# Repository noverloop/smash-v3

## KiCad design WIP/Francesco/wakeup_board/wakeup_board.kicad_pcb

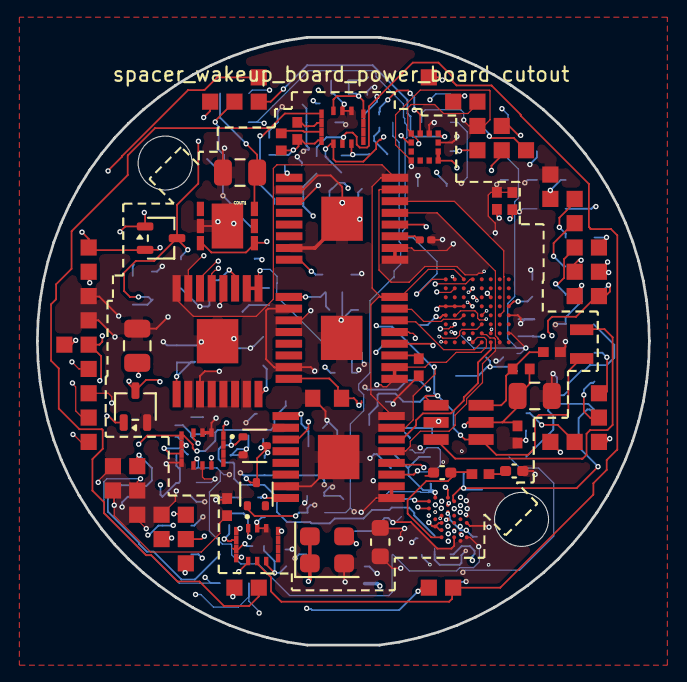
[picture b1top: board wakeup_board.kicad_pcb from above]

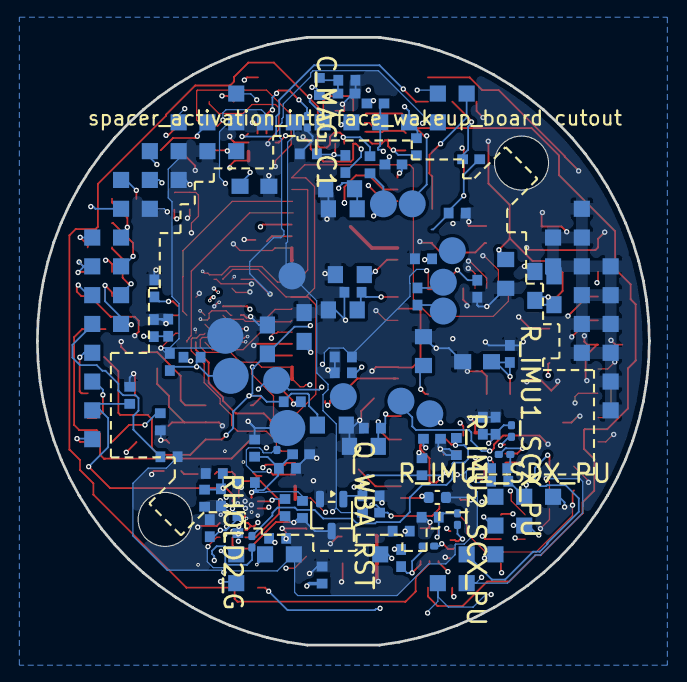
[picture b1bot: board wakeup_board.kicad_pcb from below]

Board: 14 copper layers, 34.0 x 33.8 mm, 127 parts (90 on the bottom side), 109 nets.

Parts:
CBOOST_IN1_1, CBOOST_IN1_2, CBOOST_IN1_3, CBOOST_IN1_4, CBOOST_IN1_5: C-Series MIL-PRF-32535 X7R 0603 2.2uF; C_0603_1608Metric
CBOOST_IN2: C0402 X7R 100nF; C_0402_1005Metric
CBOOST_OUT1: 22uF 16V X5R 0805; C_0805_2012Metric
CBOOST_OUT2: C0402 X7R 100nF; C_0402_1005Metric
CMAIN_HOLD: C0402 X7R 100nF; C_0402_1005Metric
COUT1: T491T 22uF (3528-12 thinnest variant); C_0805_2012Metric
COUT2: 22uF 16V X5R 0805; C_0805_2012Metric
COUT3: C0402 X7R 100nF; C_0402_1005Metric
C_CAM_VDD: C0402 X7R 100nF; C_0402_1005Metric
C_FIN1_DVDD, C_FIN3_DVDD, C_FIN4_DVDD: C-Series MIL-PRF-32535 X7R 0805 1uF; C_0603_1608Metric
C_FIN1_VM, C_FIN2_VM, C_FIN3_VM, C_FIN4_VM: C0402 X7R 100nF; C_0402_1005Metric
C_FIN2_DVDD: C-Series MIL-PRF-32535 X7R 0805 1uF; C_0402_1005Metric
C_FIN_VM_BULK_1, C_FIN_VM_BULK_2, C_FIN_VM_BULK_3, C_FIN_VM_BULK_4, C_FIN_VM_BULK_5: C-Series MIL-PRF-32535 X7R 0603 2.2uF; C_0603_1608Metric
C_FIN_VREF: C0402 X7R 100nF; C_0402_1005Metric
C_G0B1_FIN_BULK: C-Series MIL-PRF-32535 X7R 0805 1uF; C_0603_1608Metric
C_G0B1_FIN_NRST, C_G0B1_FIN_VDD1, C_G0B1_FIN_VDD2, C_G0B1_FIN_VREF: C0402 X7R 100nF; C_0402_1005Metric
C_IMU1_1, C_IMU2_1, C_IMU3_1: C0402 X7R 100nF; C_0402_1005Metric
C_IMU1_2, C_IMU2_2, C_IMU3_2: C-Series MIL-PRF-32535 X7R 0603 2.2uF; C_0402_1005Metric
C_IMU1_3, C_IMU2_3, C_IMU3_3: C0402 X7R 10nF; C_0402_1005Metric
C_J_HALL_FIN_VCC: C0402 X7R 100nF; C_0402_1005Metric
C_MAG1: C0402 X7R 100nF; C_0402_1005Metric
C_MAG2: C-Series MIL-PRF-32535 X7R 0805 1uF; C_0603_1608Metric
C_MAG_C1: C-Series MIL-PRF-32535 X7R 0603 220nF; R_0201_0603Metric
C_WBA_BULK_1, C_WBA_BULK_2: C-Series MIL-PRF-32535 X7R 0603 2.2uF; C_0402_1005Metric
C_WBA_HSE_VDD: C0402 X7R 100nF; C_0402_1005Metric
C_WBA_NRST: C0402 X7R 100nF; C_0402_1005Metric
C_WBA_PI1, C_WBA_PI2: SQCSVA 0.5pF; C_0402_1005Metric
C_WBA_VDD1, C_WBA_VDD2: C0402 X7R 100nF; C_0402_1005Metric
C_WBA_VDD11: C-Series MIL-PRF-32535 X7R 0603 2.2uF; C_0402_1005Metric
C_WBA_VDDA: C0402 X7R 100nF; C_0402_1005Metric
C_WBA_VDDANA: C0402 X7R 100nF; C_0402_1005Metric
C_WBA_VDDHPA: C0402 X7R 100nF; C_0402_1005Metric
C_WBA_VDDRF: C0402 X7R 100nF; C_0402_1005Metric
C_WBA_VDDRFPA: C0402 X7R 100nF; C_0402_1005Metric
C_WBA_VDDSMPS: C0402 X7R 100nF; C_0402_1005Metric
D_NFC_WAKE: BAT64-06-TP; SOT-523
J_HALL_FIN_GND: J_HALL_FIN_GND; Pogo_Pad_D2.0mm
J_HALL_FIN_OUT: J_HALL_FIN_OUT; Pogo_Pad_D2.0mm
J_HALL_FIN_VCC: J_HALL_FIN_VCC; Pogo_Pad_D2.0mm
J_wakeup_board_spacer_wakeup_board_power_board: LGA_lands; J_wakeup_board_spacer_wakeup_board_power_board
L_PWR: TMS201210ALM-2R2MTAA; L_2012_2.0x1.25mm
L_WBA_PI: WE-KI 0402 2.7nH (74479xxxxx family); L_0402_1005Metric
L_WBA_SMPS: TMS201210ALM-2R2MTAA; L_0603_1608Metric
P_wakeup_board_spacer_activation_interface_wakeup_board: LGA_lands; P_wakeup_board_spacer_activation_interface_wakeup_board
QHOLD: BSS138LT1G; SOT-323_SC-70
QHOLD2: BSS138LT1G; SOT-523
QMAIN: DMP2165UW-7; SOT-323_SC-70
Q_WBA_RST: BSS138LT1G; SOT-323_SC-70
RHOLD2_G: CRCW0402 100 1% e3; R_0201_0603Metric
RHOLD2_PD: CRCW0402 100k 1% e3; R_0402_1005Metric
RHOLD_AON: CRCW0402 1k 1% e3; R_0402_1005Metric
RHOLD_G: CRCW0402 100 1% e3; R_0402_1005Metric
RHOLD_PD: CRCW0402 100k 1% e3; R_0402_1005Metric
RMAIN_PU: CRCW0402 1M 1% e3; R_0402_1005Metric
RPU_I2C2_SCL, RPU_I2C2_SDA, RPU_I2C3_SCL, RPU_I2C3_SDA: CRCW0402 4.7k 1% e3; R_0402_1005Metric
RPU_SCL_EXT: CRCW0402 4.7k 1% e3; R_0402_1005Metric
RPU_SDA_EXT: CRCW0402 4.7k 1% e3; R_0402_1005Metric
R_BOOST_FB1: CRCW0402 220k 1% e3; R_0402_1005Metric
R_BOOST_FB2: CRCW0402 100k 1% e3; R_0402_1005Metric
R_FIN1_DECAY, R_FIN4_DECAY: CRCW0402 44.2k 1% e3; R_0402_1005Metric
R_FIN2_DECAY, R_FIN3_DECAY: CRCW0402 44.2k 1% e3; R_0201_0603Metric
R_G0B1_FIN_NRST: CRCW0402 10k 1% e3; R_0402_1005Metric
R_IMU1_SCX_PU, R_IMU1_SDX_PU, R_IMU2_SCX_PU, R_IMU2_SDX_PU: CRCW0402 10k 1% e3; R_0201_0603Metric
R_IMU3_SCX_PU, R_IMU3_SDX_PU: CRCW0402 10k 1% e3; R_0402_1005Metric
R_J_HALL_FIN_PU: CRCW0402 10k 1% e3; R_0402_1005Metric
R_NFC_WAKE: CRCW0402 3.3k 1% e3; R_0402_1005Metric
R_WBARST_PD: CRCW0402 100k 1% e3; R_0402_1005Metric
R_WBA_BOOT0: CRCW0402 10k 1% e3; R_0402_1005Metric
R_WBA_NRST: CRCW0402 10k 1% e3; R_0402_1005Metric
R_WILK_ISO: CRCW0402 100 1% e3; R_0402_1005Metric
TP_3V3: TP_3V3; TestPoint_Pad_D1.5mm
TP_BAT: TP_BAT; TestPoint_Pad_D1.5mm
TP_IMU1_INT: TP_IMU1_INT; TestPoint_Pad_D1.5mm
TP_IMU2_INT: TP_IMU2_INT; TestPoint_Pad_D1.5mm
TP_IMU3_INT: TP_IMU3_INT; TestPoint_Pad_D1.5mm
TP_NFC_GPO: TP_NFC_GPO; TestPoint_Pad_D1.5mm
TP_WILK_A: TP_WILK_A; TestPoint_Pad_D1.5mm
TP_WILK_B: TP_WILK_B; TestPoint_Pad_D1.5mm
TP_YAGI_RF_A: TP_YAGI_RF_A; TestPoint_Pad_D1.5mm
TP_YAGI_RF_B: TP_YAGI_RF_B; TestPoint_Pad_D1.5mm
U_BOOST: MCP1640CT-I/CHY; SOT95P270X145-6N
U_FIN1, U_FIN2, U_FIN3, U_FIN4: DRV8428EPWPR; SOP65P640X120-17N
U_G0B1_FIN: STM32G0B1REI6N; BGA64C50P8X8_500X500X60
U_IMU1, U_IMU2, U_IMU3: ISM330DHCXTR; LSM6DS3USTR (LGA-14)
U_MAG: IIS2MDCTR
U_PWR: LDL112PV33R; SON95P300X300X100-7N-D
U_WBA: STM32WBA55HGF6TR; BGA41C35P13X7_298X276X50
Y_WBA_HSE: DSC1001CI5-032.0000; Oscillator_SMD_SiT_PQFN-4Pin_2.5x2.0mm

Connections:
3V3: COUT1.1, COUT2.1, COUT3.1, C_G0B1_FIN_BULK.1, C_G0B1_FIN_VDD1.1, C_G0B1_FIN_VDD2.1, C_G0B1_FIN_VREF.1, C_IMU1_1.1, C_IMU1_2.1, C_IMU1_3.1, C_IMU2_1.1, C_IMU2_2.1, C_IMU2_3.1, C_IMU3_1.1, C_IMU3_2.1, C_IMU3_3.1, C_J_HALL_FIN_VCC.1, C_MAG1.1, C_MAG2.1, J_HALL_FIN_VCC.1, J_wakeup_board_spacer_wakeup_board_powe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.1, J_wakeup_board_spacer_wakeup_board_powe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.49, P_wakeup_board_spacer_activation_interf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.1, P_wakeup_board_spacer_activation_interf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.42, P_wakeup_board_spacer_activation_interf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.47, RPU_I2C2_SCL.1, RPU_I2C2_SDA.1, RPU_I2C3_SCL.1, RPU_I2C3_SDA.1, RPU_SCL_EXT.1, RPU_SDA_EXT.1, R_G0B1_FIN_NRST.1, R_IMU1_SCX_PU.1, R_IMU1_SDX_PU.1, R_IMU2_SCX_PU.1, R_IMU2_SDX_PU.1, R_IMU3_SCX_PU.1, R_IMU3_SDX_PU.1, R_J_HALL_FIN_PU.1, TP_3V3.1, U_G0B1_FIN.D1, U_G0B1_FIN.D2, U_G0B1_FIN.D3, U_G0B1_FIN.D8, U_IMU1.5, U_IMU1.8, U_IMU1.12, U_IMU2.5, U_IMU2.8, U_IMU2.12, U_IMU3.1, U_IMU3.5, U_IMU3.8, U_IMU3.12, U_MAG.3, U_MAG.9, U_MAG.10, U_PWR.4
3V3_AON: C_WBA_BULK_1.1, C_WBA_BULK_2.1, C_WBA_HSE_VDD.1, C_WBA_VDD1.1, C_WBA_VDD2.1, C_WBA_VDDA.1, C_WBA_VDDANA.1, C_WBA_VDDHPA.1, C_WBA_VDDRF.1, C_WBA_VDDRFPA.1, C_WBA_VDDSMPS.1, P_wakeup_board_spacer_activation_interf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.2, P_wakeup_board_spacer_activation_interf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.43, R_WBA_NRST.1, U_WBA.A6, U_WBA.A10, U_WBA.B5, U_WBA.B13, U_WBA.C4, U_WBA.C6, U_WBA.E12, U_WBA.G4, Y_WBA_HSE.1, Y_WBA_HSE.4
ACTIVATE_CONFIRM: J_wakeup_board_spacer_wakeup_board_powe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.2, P_wakeup_board_spacer_activation_interf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.3
ACTIVATE_SET: J_wakeup_board_spacer_wakeup_board_powe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.3, P_wakeup_board_spacer_activation_interf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.4
AON_EN: P_wakeup_board_spacer_activation_interf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.5, RHOLD_AON.2
BAT_PROT: J_wakeup_board_spacer_wakeup_board_powe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.4, J_wakeup_board_spacer_wakeup_board_powe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.50, P_wakeup_board_spacer_activation_interf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.6, P_wakeup_board_spacer_activation_interf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.44, QMAIN.2, TP_BAT.1
BAT_RAW: J_wakeup_board_spacer_wakeup_board_powe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.5, J_wakeup_board_spacer_wakeup_board_powe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.51, P_wakeup_board_spacer_activation_interf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.7, P_wakeup_board_spacer_activation_interf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.45, RMAIN_PU.1
BOOST_FB: R_BOOST_FB1.2, R_BOOST_FB2.1, U_BOOST.4
BOOST_OUT: CBOOST_OUT1.1, CBOOST_OUT2.1, R_BOOST_FB1.1, U_BOOST.5, U_PWR.1, U_PWR.6
BOOST_SW: L_PWR.2, U_BOOST.1
BOOT0: J_wakeup_board_spacer_wakeup_board_powe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.6, P_wakeup_board_spacer_activation_interf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.8
COMP_1V8: C_CAM_VDD.1, J_wakeup_board_spacer_wakeup_board_powe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.7
COMP_5V: J_wakeup_board_spacer_wakeup_board_powe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.8, P_wakeup_board_spacer_activation_interf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.9, P_wakeup_board_spacer_activation_interf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.46
COMP_5V_RAW: C_FIN1_VM.1, C_FIN2_VM.1, C_FIN3_VM.1, C_FIN4_VM.1, C_FIN_VM_BULK_1.1, C_FIN_VM_BULK_2.1, C_FIN_VM_BULK_3.1, C_FIN_VM_BULK_4.1, C_FIN_VM_BULK_5.1, J_wakeup_board_spacer_wakeup_board_powe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.9, U_FIN1.1, U_FIN2.1, U_FIN3.1, U_FIN4.1
COMP_OUT: J_wakeup_board_spacer_wakeup_board_powe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.10, P_wakeup_board_spacer_activation_interf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.10
COMP_SWDCLK: J_wakeup_board_spacer_wakeup_board_powe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.11, P_wakeup_board_spacer_activation_interf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.11
COMP_SWDIO: J_wakeup_board_spacer_wakeup_board_powe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.12, P_wakeup_board_spacer_activation_interf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.12
EXT_CAN_RX: J_wakeup_board_spacer_wakeup_board_powe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.13, P_wakeup_board_spacer_activation_interf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.13
EXT_CAN_TX: J_wakeup_board_spacer_wakeup_board_powe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.14, P_wakeup_board_spacer_activation_interf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.14
FIN1_AEN: U_FIN1.15, U_G0B1_FIN.E3
FIN1_AOUT1: P_wakeup_board_spacer_activation_interf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.15, U_FIN1.3
FIN1_APH: U_FIN1.14, U_G0B1_FIN.H5
FIN1_BEN: U_FIN1.13, U_G0B1_FIN.F5
FIN1_BPH: U_FIN1.12, U_G0B1_FIN.B4
FIN1_DECAY: R_FIN1_DECAY.1, U_FIN1.11
FIN1_DVDD: C_FIN1_DVDD.1, U_FIN1.8
FIN2_AEN: U_FIN2.15, U_G0B1_FIN.F2
FIN2_AOUT1: P_wakeup_board_spacer_activation_interf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.16, U_FIN2.3
FIN2_APH: U_FIN2.14, U_G0B1_FIN.H6
FIN2_BEN: U_FIN2.13, U_G0B1_FIN.G5
FIN2_BPH: U_FIN2.12, U_G0B1_FIN.C4
FIN2_DECAY: R_FIN2_DECAY.1, U_FIN2.11
FIN2_DVDD: C_FIN2_DVDD.1, U_FIN2.8
FIN3_AEN: U_FIN3.15, U_G0B1_FIN.G2
FIN3_AOUT1: P_wakeup_board_spacer_activation_interf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.17, U_FIN3.3
FIN3_APH: U_FIN3.14, U_G0B1_FIN.E7
FIN3_BEN: U_FIN3.13, U_G0B1_FIN.H7
FIN3_BPH: U_FIN3.12, U_G0B1_FIN.D4
FIN3_DECAY: R_FIN3_DECAY.1, U_FIN3.11
FIN3_DVDD: C_FIN3_DVDD.1, U_FIN3.8
FIN4_AEN: U_FIN4.15, U_G0B1_FIN.H1
FIN4_AOUT1: P_wakeup_board_spacer_activation_interf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.18, U_FIN4.3
FIN4_APH: U_FIN4.14, U_G0B1_FIN.E5
FIN4_BEN: U_FIN4.13, U_G0B1_FIN.G6
FIN4_BPH: U_FIN4.12, U_G0B1_FIN.A4
FIN4_DECAY: R_FIN4_DECAY.1, U_FIN4.11
FIN4_DVDD: C_FIN4_DVDD.1, U_FIN4.8
FIN_HALL: J_HALL_FIN_OUT.1, P_wakeup_board_spacer_activation_interf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.19, R_J_HALL_FIN_PU.2, U_G0B1_FIN.G8
FIN_NSLEEP: U_FIN1.16, U_FIN2.16, U_FIN3.16, U_FIN4.16, U_G0B1_FIN.A3
FIN_VREF: C_FIN_VREF.1, P_wakeup_board_spacer_activation_interf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.20, U_FIN1.9, U_FIN1.10, U_FIN2.9, U_FIN2.10, U_FIN3.9, U_FIN3.10, U_FIN4.9, U_FIN4.10, U_G0B1_FIN.H4
FLEX_GND: CBOOST_IN1_1.2, CBOOST_IN1_2.2, CBOOST_IN1_3.2, CBOOST_IN1_4.2, CBOOST_IN1_5.2, CBOOST_IN2.2, CBOOST_OUT1.2, CBOOST_OUT2.2, CMAIN_HOLD.2, COUT1.2, COUT2.2, COUT3.2, C_CAM_VDD.2, C_FIN1_DVDD.2, C_FIN1_VM.2, C_FIN2_DVDD.2, C_FIN2_VM.2, C_FIN3_DVDD.2, C_FIN3_VM.2, C_FIN4_DVDD.2, C_FIN4_VM.2, C_FIN_VM_BULK_1.2, C_FIN_VM_BULK_2.2, C_FIN_VM_BULK_3.2, C_FIN_VM_BULK_4.2, C_FIN_VM_BULK_5.2, C_FIN_VREF.2, C_G0B1_FIN_BULK.2, C_G0B1_FIN_NRST.2, C_G0B1_FIN_VDD1.2, C_G0B1_FIN_VDD2.2, C_G0B1_FIN_VREF.2, C_IMU1_1.2, C_IMU1_2.2, C_IMU1_3.2, C_IMU2_1.2, C_IMU2_2.2, C_IMU2_3.2, C_IMU3_1.2, C_IMU3_2.2, C_IMU3_3.2, C_J_HALL_FIN_VCC.2, C_MAG1.2, C_MAG2.2, C_MAG_C1.2, C_WBA_BULK_1.2, C_WBA_BULK_2.2, C_WBA_HSE_VDD.2, C_WBA_NRST.2, C_WBA_PI1.2, C_WBA_PI2.2, C_WBA_VDD1.2, C_WBA_VDD2.2, C_WBA_VDD11.2, C_WBA_VDDA.2, C_WBA_VDDANA.2, C_WBA_VDDHPA.2, C_WBA_VDDRF.2, C_WBA_VDDRFPA.2, C_WBA_VDDSMPS.2, J_HALL_FIN_GND.1, J_wakeup_board_spacer_wakeup_board_powe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.15, P_wakeup_board_spacer_activation_interf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.21, P_wakeup_board_spacer_activation_interf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.48, P_wakeup_board_spacer_activation_interf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.49, P_wakeup_board_spacer_activation_interf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.50, P_wakeup_board_spacer_activation_interf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.51, P_wakeup_board_spacer_activation_interf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.52, P_wakeup_board_spacer_activation_interf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.53, P_wakeup_board_spacer_activation_interf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.54, P_wakeup_board_spacer_activation_interf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.55, P_wakeup_board_spacer_activation_interf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.56, P_wakeup_board_spacer_activation_interf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.57, P_wakeup_board_spacer_activation_interf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.58, P_wakeup_board_spacer_activation_interf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.59, P_wakeup_board_spacer_activation_interf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.60, P_wakeup_board_spacer_activation_interf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.61, P_wakeup_board_spacer_activation_interf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.62, QHOLD.2, QHOLD2.2, Q_WBA_RST.2, RHOLD2_PD.2, RHOLD_PD.2, R_BOOST_FB2.2, R_FIN1_DECAY.2, R_FIN2_DECAY.2, R_FIN3_DECAY.2, R_FIN4_DECAY.2, R_WBARST_PD.2, R_WBA_BOOT0.2, U_BOOST.2, U_FIN1.2, U_FIN1.7, U_FIN1.17, U_FIN2.2, U_FIN2.7, U_FIN2.17, U_FIN3.2, U_FIN3.7, U_FIN3.17, U_FIN4.2, U_FIN4.7, U_FIN4.17, U_G0B1_FIN.E1, U_G0B1_FIN.E8, U_IMU1.1, U_IMU1.6, U_IMU1.7, U_IMU2.1, U_IMU2.6, U_IMU2.7, U_IMU3.6, U_IMU3.7, U_MAG.6, U_MAG.8, U_PWR.2, U_PWR.7, U_WBA.A12, U_WBA.B9, U_WBA.D1, U_WBA.D3, U_WBA.D5, U_WBA.D13, U_WBA.G6, Y_WBA_HSE.2
G0B1_FIN_NRST: C_G0B1_FIN_NRST.1, R_G0B1_FIN_NRST.2, U_G0B1_FIN.E2
GPIO_EXT_0: J_wakeup_board_spacer_wakeup_board_powe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.16, P_wakeup_board_spacer_activation_interf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.22
GPIO_EXT_1: J_wakeup_board_spacer_wakeup_board_powe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.17, P_wakeup_board_spacer_activation_interf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.23
GPIO_EXT_2: J_wakeup_board_spacer_wakeup_board_powe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.18, P_wakeup_board_spacer_activation_interf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.24
GPIO_EXT_3: J_wakeup_board_spacer_wakeup_board_powe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.19, P_wakeup_board_spacer_activation_interf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.25
H3LIS_INT1: P_wakeup_board_spacer_activation_interf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.26, U_WBA.G8
H3LIS_SCL: P_wakeup_board_spacer_activation_interf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.27, U_WBA.D9
H3LIS_SDA: P_wakeup_board_spacer_activation_interf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.28, U_WBA.D11
I2C2_SCL: J_wakeup_board_spacer_wakeup_board_powe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.20, P_wakeup_board_spacer_activation_interf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.29, RPU_I2C2_SCL.2, U_IMU1.13, U_MAG.1, U_WBA.F3
I2C2_SDA: J_wakeup_board_spacer_wakeup_board_powe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.21, P_wakeup_board_spacer_activation_interf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.30, RPU_I2C2_SDA.2, U_IMU1.14, U_MAG.4, U_WBA.G2
I2C3_SCL: J_wakeup_board_spacer_wakeup_board_powe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.22, RPU_I2C3_SCL.2, U_IMU2.13, U_IMU3.13
I2C3_SDA: J_wakeup_board_spacer_wakeup_board_powe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.23, RPU_I2C3_SDA.2, U_IMU2.14, U_IMU3.14
IMU1_INT: J_wakeup_board_spacer_wakeup_board_powe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.24, TP_IMU1_INT.1, U_IMU1.4
IMU1_SCX: R_IMU1_SCX_PU.2, U_IMU1.3
IMU1_SDX: R_IMU1_SDX_PU.2, U_IMU1.2
IMU2_INT: J_wakeup_board_spacer_wakeup_board_powe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.25, TP_IMU2_INT.1, U_IMU2.4
IMU2_SCX: R_IMU2_SCX_PU.2, U_IMU2.3
IMU2_SDX: R_IMU2_SDX_PU.2, U_IMU2.2
IMU3_INT: J_wakeup_board_spacer_wakeup_board_powe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.26, TP_IMU3_INT.1, U_IMU3.4
IMU3_SCX: R_IMU3_SCX_PU.2, U_IMU3.3
IMU3_SDX: R_IMU3_SDX_PU.2, U_IMU3.2
MAG_C1_TERM: C_MAG_C1.1, U_MAG.5
MAG_DRDY: J_wakeup_board_spacer_wakeup_board_powe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.27, U_MAG.7
MAIN_SW_GATE: CMAIN_HOLD.1, D_NFC_WAKE.3, J_wakeup_board_spacer_wakeup_board_powe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.28, QHOLD.3, QHOLD2.3, QMAIN.1, RMAIN_PU.2
NFC_GPO: P_wakeup_board_spacer_activation_interf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.31, R_NFC_WAKE.2, TP_NFC_GPO.1, U_WBA.D7
NFC_WAKE_K: D_NFC_WAKE.1, P_wakeup_board_spacer_activation_interf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.32, R_NFC_WAKE.1
NRST: J_wakeup_board_spacer_wakeup_board_powe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.29, P_wakeup_board_spacer_activation_interf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.33
PWR_HOLD: J_wakeup_board_spacer_wakeup_board_powe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.30, RHOLD_G.1
QHOLD2_GATE: QHOLD2.1, RHOLD2_G.2, RHOLD2_PD.1
QHOLD_GATE: QHOLD.1, RHOLD_G.2, RHOLD_PD.1
REG_IN_MAIN: CBOOST_IN1_1.1, CBOOST_IN1_2.1, CBOOST_IN1_3.1, CBOOST_IN1_4.1, CBOOST_IN1_5.1, CBOOST_IN2.1, J_wakeup_board_spacer_wakeup_board_powe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.31, L_PWR.1, QMAIN.3, U_BOOST.3, U_BOOST.6
SWO: J_wakeup_board_spacer_wakeup_board_powe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.32, P_wakeup_board_spacer_activation_interf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.34
SYS_I2C_SCL: J_wakeup_board_spacer_wakeup_board_powe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.33, P_wakeup_board_spacer_activation_interf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.35, RPU_SCL_EXT.2
SYS_I2C_SDA: J_wakeup_board_spacer_wakeup_board_powe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.34, P_wakeup_board_spacer_activation_interf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.36, RPU_SDA_EXT.2
SYS_SPI_CS_FIN: J_wakeup_board_spacer_wakeup_board_powe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.35, P_wakeup_board_spacer_activation_interf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.37, U_G0B1_FIN.C6
SYS_SPI_MISO: J_wakeup_board_spacer_wakeup_board_powe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.36, P_wakeup_board_spacer_activation_interf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.38, U_G0B1_FIN.A1
SYS_SPI_MOSI: J_wakeup_board_spacer_wakeup_board_powe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.37, P_wakeup_board_spacer_activation_interf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.39, U_G0B1_FIN.B2
SYS_SPI_SCLK: J_wakeup_board_spacer_wakeup_board_powe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.38, P_wakeup_board_spacer_activation_interf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.40, U_G0B1_FIN.A2
USBWK_GATE: J_wakeup_board_spacer_wakeup_board_powe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.39, P_wakeup_board_spacer_activation_interf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.41
WBA_AON_HOLD: RHOLD_AON.1, U_WBA.E4
WBA_BOOT0: J_wakeup_board_spacer_wakeup_board_powe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.40, R_WBA_BOOT0.1, U_WBA.C8
WBA_HCI_IRQ: J_wakeup_board_spacer_wakeup_board_powe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.41, U_WBA.C10
WBA_HCI_MISO: J_wakeup_board_spacer_wakeup_board_powe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.42, U_WBA.F9
WBA_HCI_MOSI: J_wakeup_board_spacer_wakeup_board_powe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.43, U_WBA.G10
WBA_HCI_NSS: J_wakeup_board_spacer_wakeup_board_powe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.44, U_WBA.F13
WBA_HCI_SCK: J_wakeup_board_spacer_wakeup_board_powe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.45, U_WBA.G12
WBA_HSE_IN: U_WBA.A8, Y_WBA_HSE.3
WBA_NRST: C_WBA_NRST.1, Q_WBA_RST.3, R_WBA_NRST.2, U_WBA.E2
WBA_RF: C_WBA_PI1.1, L_WBA_PI.1, U_WBA.C2
WBA_RF_M: C_WBA_PI2.1, L_WBA_PI.2
WBA_RST_CMD: J_wakeup_board_spacer_wakeup_board_powe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.46, Q_WBA_RST.1, R_WBARST_PD.1
WBA_UART_RX: J_wakeup_board_spacer_wakeup_board_powe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.47, U_WBA.E10
WBA_UART_TX: J_wakeup_board_spacer_wakeup_board_powe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.48, U_WBA.F11
WBA_VDD11: C_WBA_VDD11.1, L_WBA_SMPS.2, U_WBA.B11
WBA_VLX: L_WBA_SMPS.1, U_WBA.C12
WBA_WAKE: RHOLD2_G.1, U_WBA.F5
YAGI_WILK_A: R_WILK_ISO.1, TP_WILK_A.1
YAGI_WILK_B: R_WILK_ISO.2, TP_WILK_B.1

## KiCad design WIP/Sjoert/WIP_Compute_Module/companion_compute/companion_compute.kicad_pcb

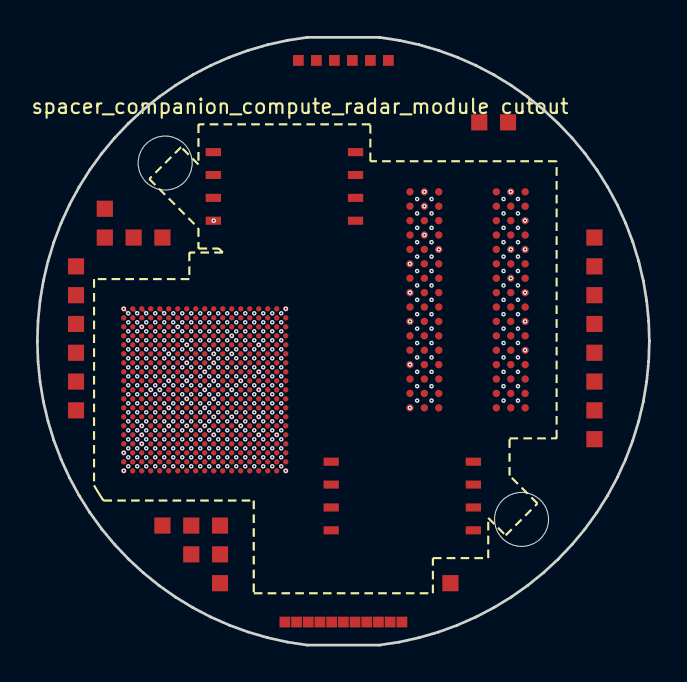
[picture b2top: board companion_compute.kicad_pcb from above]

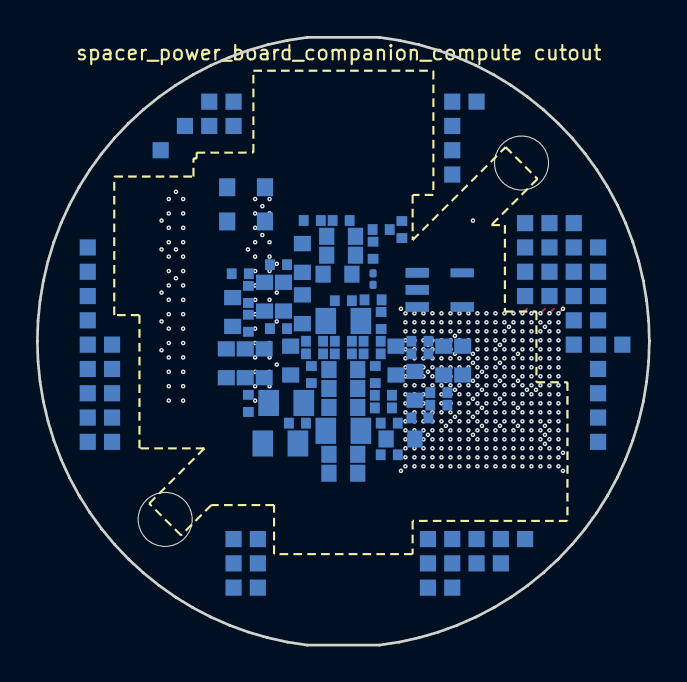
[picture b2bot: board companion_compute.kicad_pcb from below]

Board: 14 copper layers, 34.0 x 33.8 mm, 69 parts (62 on the bottom side), 144 nets.

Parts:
C_DDR_BULK1_1, C_DDR_BULK1_2, C_DDR_BULK1_3, C_DDR_BULK1_4, C_DDR_BULK1_5, C_DDR_BULK2_1, C_DDR_BULK2_2, C_DDR_BULK2_3, C_DDR_BULK2_4, C_DDR_BULK2_5: C-Series MIL-PRF-32535 X7R 0603 2.2uF; C_0603_1608Metric
C_DDR_VDD1, C_DDR_VDD2, C_DDR_VDD3, C_DDR_VDD4, C_DDR_VDD5, C_DDR_VDD6: C0402 X7R 100nF; C_0402_1005Metric
C_DDR_VPP1: C-Series MIL-PRF-32535 X7R 0805 1uF; C_0805_2012Metric
C_DDR_VPP2: C0402 X7R 100nF; C_0402_1005Metric
C_DDR_VREFCA: C0402 X7R 100nF; C_0402_1005Metric
C_MPU_0V82_1, C_MPU_0V82_2, C_MPU_5V2, C_MPU_18A_1, C_MPU_18A_2, C_MPU_33b: C0402 X7R 100nF; C_0402_1005Metric
C_MPU_0V82_BULK, C_MPU_5V_1, C_MPU_5V_2, C_MPU_5V_3, C_MPU_5V_4, C_MPU_5V_5, C_MPU_33_1, C_MPU_33_2, C_MPU_33_3, C_MPU_33_4, C_MPU_33_5: C-Series MIL-PRF-32535 X7R 0603 2.2uF; C_0603_1608Metric
C_MPU_HSE_VDD: C0402 X7R 100nF; C_0402_1005Metric
C_MPU_LSE_VDD: C0402 X7R 100nF; C_0402_1005Metric
C_MPU_NRST: C0402 X7R 100nF; C_0402_1005Metric
C_MPU_QDDR_1, C_MPU_QDDR_2: C0402 X7R 100nF; C_0402_1005Metric
C_MPU_V08CAP: C-Series MIL-PRF-32535 X7R 0603 2.2uF; C_0603_1608Metric
C_NAND_A_BULK: C-Series MIL-PRF-32535 X7R 0805 1uF; C_0805_2012Metric
C_NAND_A_VCC: C0402 X7R 100nF; C_0402_1005Metric
C_NAND_B_BULK: C-Series MIL-PRF-32535 X7R 0805 1uF; C_0805_2012Metric
C_NAND_B_VCC: C0402 X7R 100nF; C_0402_1005Metric
C_USB_18: C0402 X7R 100nF; C_0402_1005Metric
C_USB_33: C-Series MIL-PRF-32535 X7R 0805 1uF; C_0805_2012Metric
J_FLEXL_companion_compute__camera_module: FLEX_LAUNCH; J_FLEXL_companion_compute__camera_module
J_FLEXL_companion_compute__qpd_module: FLEX_LAUNCH; J_FLEXL_companion_compute__qpd_module
J_companion_compute_spacer_companion_compute_radar_module: LGA_lands; J_companion_compute_spacer_companion_compute_radar_module
P_companion_compute_spacer_power_board_companion_compute: LGA_lands; P_companion_compute_spacer_power_board_companion_compute
R_DDR_ALERTN_PU: CRCW0402 10k 1% e3; R_0402_1005Metric
R_DDR_RESETN_PD: CRCW0402 10k 1% e3; R_0402_1005Metric
R_DDR_VREFCA_BOT: CRCW0402 1k 1% e3; R_0402_1005Metric
R_DDR_VREFCA_TOP: CRCW0402 1k 1% e3; R_0402_1005Metric
R_DDR_ZQ: CRCW0402 240 1% e3; R_0402_1005Metric
R_MPU_BOOT0: CRCW0402 10k 1% e3; R_0402_1005Metric
R_MPU_CSI_REXT: CRCW0402 12k 1% e3; R_0402_1005Metric
R_MPU_DDR_ZQ: CRCW0201 240 1% e3; R_0201_0603Metric
R_MPU_NRST: CRCW0402 10k 1% e3; R_0402_1005Metric
R_MPU_TXRTUNE: CRCW0402 200 1% e3; R_0402_1005Metric
R_USB_VBUS_PD: CRCW0402 100k 1% e3; R_0402_1005Metric
U_DDR4: KTDM4G4B626BGIEAT; BGA96C80P9X16_750X1300X100
U_MPU: STM32MP255DAL3
U_NAND_A: MT29F4G01ABAFDWB-IT_F; SON127P800X600X65-8N
U_NAND_B: MT29F4G01ABAFDWB-IT_F; SON127P800X600X65-8N
Y_MPU_HSE: DSC1001CI5-040.0000; DSC1001CI50080000
Y_MPU_LSE: SiT1630AE-S6-DCC-32.768E; SOT-23_5pins

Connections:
3V3: J_FLEXL_companion_compute__qpd_module.1, P_companion_compute_spacer_power_board_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.1, P_companion_compute_spacer_power_board_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.57
ACTIVATE_CONFIRM: P_companion_compute_spacer_power_board_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.2, U_MPU.C10
ACTIVATE_SET: P_companion_compute_spacer_power_board_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.3, U_MPU.B13
AWR_DRDY: J_companion_compute_spacer_companion_co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.1, U_MPU.U8
AWR_FAULT: J_companion_compute_spacer_companion_co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.2, U_MPU.D5
AWR_NRESET: J_companion_compute_spacer_companion_co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.3, U_MPU.D4
AWR_SPI_CLK: J_companion_compute_spacer_companion_co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.4, U_MPU.B10
AWR_SPI_CS: J_companion_compute_spacer_companion_co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.5, U_MPU.A10
AWR_SPI_MISO: J_companion_compute_spacer_companion_co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.6, U_MPU.A14
AWR_SPI_MOSI: J_companion_compute_spacer_companion_co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.7, U_MPU.B14
BAT_ISO_DRIVE: P_companion_compute_spacer_power_board_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.4, U_MPU.F14
BAT_PROT: J_companion_compute_spacer_companion_co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.8, J_companion_compute_spacer_companion_co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.17, P_companion_compute_spacer_power_board_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.5, P_companion_compute_spacer_power_board_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.58
BOOT0: P_companion_compute_spacer_power_board_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.6, R_MPU_BOOT0.2, U_MPU.T2
CAM_CSI_CLK_N: J_FLEXL_companion_compute__camera_module.1, U_MPU.C2
CAM_CSI_CLK_P: J_FLEXL_companion_compute__camera_module.2, U_MPU.C1
CAM_CSI_D0_N: J_FLEXL_companion_compute__camera_module.3, U_MPU.E1
CAM_CSI_D0_P: J_FLEXL_companion_compute__camera_module.4, U_MPU.E2
CAM_CSI_D1_N: J_FLEXL_companion_compute__camera_module.5, U_MPU.D2
CAM_CSI_D1_P: J_FLEXL_companion_compute__camera_module.6, U_MPU.D1
CAM_EXTCLK: J_FLEXL_companion_compute__camera_module.7, U_MPU.K9
COMP_0V9: P_companion_compute_spacer_power_board_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.8, P_companion_compute_spacer_power_board_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.60, U_MPU.E13, U_MPU.G13, U_MPU.J13, U_MPU.L13, U_MPU.M13
COMP_0V82: C_MPU_0V82_1.1, C_MPU_0V82_2.1, C_MPU_0V82_BULK.1, P_companion_compute_spacer_power_board_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.7, P_companion_compute_spacer_power_board_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.59, U_MPU.B1, U_MPU.C6, U_MPU.G10, U_MPU.H11, U_MPU.J1, U_MPU.J10, U_MPU.K11, U_MPU.L10, U_MPU.M11, U_MPU.N8, U_MPU.N10, U_MPU.N14, U_MPU.P11, U_MPU.P13, U_MPU.R10, U_MPU.T14, U_MPU.U12, U_MPU.W16
COMP_1V2: C_DDR_BULK1_1.1, C_DDR_BULK1_2.1, C_DDR_BULK1_3.1, C_DDR_BULK1_4.1, C_DDR_BULK1_5.1, C_DDR_BULK2_1.1, C_DDR_BULK2_2.1, C_DDR_BULK2_3.1, C_DDR_BULK2_4.1, C_DDR_BULK2_5.1, C_DDR_VDD1.1, C_DDR_VDD2.1, C_DDR_VDD3.1, C_DDR_VDD4.1, C_DDR_VDD5.1, C_DDR_VDD6.1, C_MPU_QDDR_1.1, C_MPU_QDDR_2.1, J_FLEXL_companion_compute__camera_module.8, P_companion_compute_spacer_power_board_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.9, P_companion_compute_spacer_power_board_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.61, R_DDR_ALERTN_PU.2, R_DDR_VREFCA_TOP.1, U_DDR4.A1, U_DDR4.A9, U_DDR4.B3, U_DDR4.B9, U_DDR4.C1, U_DDR4.D1, U_DDR4.D9, U_DDR4.F2, U_DDR4.F8, U_DDR4.G1, U_DDR4.G7, U_DDR4.G9, U_DDR4.J1, U_DDR4.J2, U_DDR4.J8, U_DDR4.J9, U_DDR4.L1, U_DDR4.L9, U_DDR4.R1, U_DDR4.T9, U_MPU.F16, U_MPU.J16, U_MPU.L16, U_MPU.M16, U_MPU.P16, U_MPU.T16
COMP_1V8: C_MPU_18A_1.1, C_MPU_18A_2.1, C_USB_18.1, J_FLEXL_companion_compute__camera_module.9, P_companion_compute_spacer_power_board_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.10, P_companion_compute_spacer_power_board_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.62, U_MPU.C5, U_MPU.D3, U_MPU.D16, U_MPU.E15, U_MPU.G6, U_MPU.H6, U_MPU.J4, U_MPU.N5, U_MPU.N6, U_MPU.R13, U_MPU.T13, U_MPU.U2
COMP_2V8: J_FLEXL_companion_compute__camera_module.10, P_companion_compute_spacer_power_board_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.11, P_companion_compute_spacer_power_board_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.63
COMP_3V3: C_MPU_33_1.1, C_MPU_33_2.1, C_MPU_33_3.1, C_MPU_33_4.1, C_MPU_33_5.1, C_MPU_33b.1, C_MPU_HSE_VDD.1, C_MPU_LSE_VDD.1, C_NAND_A_BULK.1, C_NAND_A_VCC.1, C_NAND_B_BULK.1, C_NAND_B_VCC.1, C_USB_33.1, J_companion_compute_spacer_companion_co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.9, J_companion_compute_spacer_companion_co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.18, P_companion_compute_spacer_power_board_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.12, P_companion_compute_spacer_power_board_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.64, R_MPU_NRST.1, R_USB_VBUS_PD.1, U_MPU.D6, U_MPU.D10, U_MPU.E6, U_MPU.E10, U_MPU.F8, U_MPU.F10, U_MPU.H8, U_MPU.K8, U_MPU.L6, U_MPU.R6, U_MPU.R14, U_MPU.U11, U_NAND_A.8, U_NAND_B.8, Y_MPU_HSE.1, Y_MPU_HSE.4, Y_MPU_LSE.4
COMP_5V: C_MPU_5V2.1, C_MPU_5V_1.1, C_MPU_5V_2.1, C_MPU_5V_3.1, C_MPU_5V_4.1, C_MPU_5V_5.1, P_companion_compute_spacer_power_board_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.13, P_companion_compute_spacer_power_board_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.65
COMP_HSE_IN: U_MPU.R1, Y_MPU_HSE.3
COMP_LSE_IN: U_MPU.M2, Y_MPU_LSE.5
COMP_OUT: P_companion_compute_spacer_power_board_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.14, U_MPU.B12
COMP_SWDCLK: P_companion_compute_spacer_power_board_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.15, U_MPU.W4
COMP_SWDIO: P_companion_compute_spacer_power_board_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.16, U_MPU.W2
COMP_VPP: C_DDR_VPP1.1, C_DDR_VPP2.1, P_companion_compute_spacer_power_board_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.17, P_companion_compute_spacer_power_board_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.66, U_DDR4.B1, U_DDR4.R9
CSI_REXT: R_MPU_CSI_REXT.1, U_MPU.E3
DDR4_A0: U_DDR4.P3, U_MPU.E19
DDR4_A1: U_DDR4.P7, U_MPU.G18
DDR4_A2: U_DDR4.R3, U_MPU.N18
DDR4_A3: U_DDR4.N7, U_MPU.M18
DDR4_A4: U_DDR4.N3, U_MPU.K19
DDR4_A5: U_DDR4.P8, U_MPU.F19
DDR4_A6: U_DDR4.P2, U_MPU.P19
DDR4_A7: U_DDR4.R8, U_MPU.G19
DDR4_A8: U_DDR4.R2, U_MPU.M19
DDR4_A9: U_DDR4.R7, U_MPU.P18
DDR4_A10: U_DDR4.M3, U_MPU.H18
DDR4_A11: U_DDR4.T2, U_MPU.H17
DDR4_A12: U_DDR4.M7, U_MPU.R19
DDR4_A13: U_DDR4.T8, U_MPU.H19
DDR4_ACT_N: U_DDR4.L3, U_MPU.L19
DDR4_ALERT_N: R_DDR_ALERTN_PU.1, U_DDR4.P9, U_MPU.H7
DDR4_BA0: U_DDR4.N2, U_MPU.J18
DDR4_BA1: U_DDR4.N8, U_MPU.N19
DDR4_BG0: U_DDR4.M2, U_MPU.R17
DDR4_CAS_N_A15: U_DDR4.M8, U_MPU.L18
DDR4_CKE: U_DDR4.K2, U_MPU.F17
DDR4_CK_C: U_DDR4.K8, U_MPU.L17
DDR4_CK_T: U_DDR4.K7, U_MPU.M17
DDR4_CS_N: U_DDR4.L7, U_MPU.J17
DDR4_DM0_N: U_DDR4.E7, U_MPU.T17
DDR4_DM1_N: U_DDR4.E2, U_MPU.C19
DDR4_DQ0: U_DDR4.F7, U_MPU.W18
DDR4_DQ1: U_DDR4.H8, U_MPU.W17
DDR4_DQ2: U_DDR4.H7, U_MPU.V17
DDR4_DQ3: U_DDR4.J7, U_MPU.U17
DDR4_DQ4: U_DDR4.J3, U_MPU.T19
DDR4_DQ5: U_DDR4.H2, U_MPU.T18
DDR4_DQ6: U_DDR4.H3, U_MPU.U19
DDR4_DQ7: U_DDR4.G2, U_MPU.U18
DDR4_DQ8: U_DDR4.D7, U_MPU.C17
DDR4_DQ9: U_DDR4.B8, U_MPU.A18
DDR4_DQ10: U_DDR4.C7, U_MPU.B17
DDR4_DQ11: U_DDR4.C8, U_MPU.A17
DDR4_DQ12: U_DDR4.C3, U_MPU.D19
DDR4_DQ13: U_DDR4.D3, U_MPU.D18
DDR4_DQ14: U_DDR4.C2, U_MPU.D17
DDR4_DQ15: U_DDR4.A3, U_MPU.C18
DDR4_DQS0_C: U_DDR4.F3, U_MPU.V18
DDR4_DQS0_T: U_DDR4.G3, U_MPU.V19
DDR4_DQS1_C: U_DDR4.A7, U_MPU.B18
DDR4_DQS1_T: U_DDR4.B7, U_MPU.B19
DDR4_ODT: U_DDR4.K3, U_MPU.J19
DDR4_PAR: U_DDR4.T3, U_MPU.E18
DDR4_RAS_N_A16: U_DDR4.L8, U_MPU.F18
DDR4_RESET_N: R_DDR_RESETN_PD.1, U_DDR4.P1, U_MPU.E17
DDR4_VREFCA: C_DDR_VREFCA.1, R_DDR_VREFCA_BOT.1, R_DDR_VREFCA_TOP.2, U_DDR4.M1, U_MPU.K17
DDR4_WE_N_A14: U_DDR4.L2, U_MPU.K18
DDR4_ZQ_CAL: R_DDR_ZQ.1, U_DDR4.F9
EXT_CAN_RX: P_companion_compute_spacer_power_board_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.18, U_MPU.A13
EXT_CAN_TX: P_companion_compute_spacer_power_board_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.19, U_MPU.A11
FLEX_GND: C_DDR_BULK1_1.2, C_DDR_BULK1_2.2, C_DDR_BULK1_3.2, C_DDR_BULK1_4.2, C_DDR_BULK1_5.2, C_DDR_BULK2_1.2, C_DDR_BULK2_2.2, C_DDR_BULK2_3.2, C_DDR_BULK2_4.2, C_DDR_BULK2_5.2, C_DDR_VDD1.2, C_DDR_VDD2.2, C_DDR_VDD3.2, C_DDR_VDD4.2, C_DDR_VDD5.2, C_DDR_VDD6.2, C_DDR_VPP1.2, C_DDR_VPP2.2, C_DDR_VREFCA.2, C_MPU_0V82_1.2, C_MPU_0V82_2.2, C_MPU_0V82_BULK.2, C_MPU_5V2.2, C_MPU_5V_1.2, C_MPU_5V_2.2, C_MPU_5V_3.2, C_MPU_5V_4.2, C_MPU_5V_5.2, C_MPU_18A_1.2, C_MPU_18A_2.2, C_MPU_33_1.2, C_MPU_33_2.2, C_MPU_33_3.2, C_MPU_33_4.2, C_MPU_33_5.2, C_MPU_33b.2, C_MPU_HSE_VDD.2, C_MPU_LSE_VDD.2, C_MPU_NRST.2, C_MPU_QDDR_1.2, C_MPU_QDDR_2.2, C_MPU_V08CAP.2, C_NAND_A_BULK.2, C_NAND_A_VCC.2, C_NAND_B_BULK.2, C_NAND_B_VCC.2, C_USB_18.2, C_USB_33.2, J_FLEXL_companion_compute__camera_module.11, J_FLEXL_companion_compute__qpd_module.2, J_companion_compute_spacer_companion_co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.10, J_companion_compute_spacer_companion_co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.20, J_companion_compute_spacer_companion_co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.21, J_companion_compute_spacer_companion_co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.22, J_companion_compute_spacer_companion_co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.23, J_companion_compute_spacer_companion_co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.24, J_companion_compute_spacer_companion_co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.25, J_companion_compute_spacer_companion_co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.26, J_companion_compute_spacer_companion_co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.27, P_companion_compute_spacer_power_board_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.20, R_DDR_RESETN_PD.2, R_DDR_VREFCA_BOT.2, R_DDR_ZQ.2, R_MPU_BOOT0.1, R_MPU_CSI_REXT.2, R_MPU_DDR_ZQ.2, R_MPU_TXRTUNE.2, U_DDR4.A2, U_DDR4.A8, U_DDR4.B2, U_DDR4.C9, U_DDR4.D2, U_DDR4.D8, U_DDR4.E1, U_DDR4.E3, U_DDR4.E8, U_DDR4.E9, U_DDR4.F1, U_DDR4.G8, U_DDR4.H1, U_DDR4.H9, U_DDR4.K1, U_DDR4.K9, U_DDR4.M9, U_DDR4.N1, U_DDR4.N9, U_DDR4.T1, U_MPU.A1, U_MPU.A19, U_MPU.C3, U_MPU.C7, U_MPU.D13, U_MPU.E8, U_MPU.E16, U_MPU.F6, U_MPU.F11, U_MPU.F13, U_MPU.G8, U_MPU.G11, U_MPU.H10, U_MPU.H13, U_MPU.H16, U_MPU.J6, U_MPU.J8, U_MPU.J11, U_MPU.J14, U_MPU.K4, U_MPU.K5, U_MPU.K10, U_MPU.K13, U_MPU.K16, U_MPU.L8, U_MPU.L11, U_MPU.M6, U_MPU.M10, U_MPU.N11, U_MPU.N13, U_MPU.N16, U_MPU.P3, U_MPU.P6, U_MPU.P8, U_MPU.P10, U_MPU.P14, U_MPU.R3, U_MPU.R11, U_MPU.R16, U_MPU.R18, U_MPU.T3, U_MPU.U1, U_MPU.W1, U_MPU.W19, U_NAND_A.4, U_NAND_B.4, Y_MPU_HSE.2, Y_MPU_LSE.1, Y_MPU_LSE.2, Y_MPU_LSE.3
GPIO_EXT_0: P_companion_compute_spacer_power_board_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.21, U_MPU.D7
GPIO_EXT_1: P_companion_compute_spacer_power_board_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.22, U_MPU.D8
GPIO_EXT_2: P_companion_compute_spacer_power_board_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.23, U_MPU.D9
GPIO_EXT_3: P_companion_compute_spacer_power_board_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.24, U_MPU.E11
H3LIS_INT1: P_companion_compute_spacer_power_board_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.25, U_MPU.D11
I2C2_SCL: P_companion_compute_spacer_power_board_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.26, U_MPU.B9
I2C2_SDA: P_companion_compute_spacer_power_board_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.27, U_MPU.C9
I2C3_SCL: P_companion_compute_spacer_power_board_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.28, U_MPU.L15
I2C3_SDA: P_companion_compute_spacer_power_board_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.29, U_MPU.L14
IMU1_INT: P_companion_compute_spacer_power_board_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.30, U_MPU.C14
IMU2_INT: P_companion_compute_spacer_power_board_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.31, U_MPU.C15
IMU3_INT: P_companion_compute_spacer_power_board_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.32, U_MPU.D12
IR_TX: J_companion_compute_spacer_companion_co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.11, P_companion_compute_spacer_power_board_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.33
IR_WAKE: J_companion_compute_spacer_companion_co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.12, P_companion_compute_spacer_power_board_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.34
MAG_DRDY: P_companion_compute_spacer_power_board_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.35, U_MPU.C13
MPU_DDR_ZQ: R_MPU_DDR_ZQ.1, U_MPU.G16
NAND_OSPI_CLK: U_MPU.G9, U_NAND_A.6, U_NAND_B.6
NAND_OSPI_CS0: U_MPU.E14, U_NAND_A.1
NAND_OSPI_CS1: U_MPU.F15, U_NAND_B.1
NAND_OSPI_IO0: U_MPU.D14, U_NAND_A.5, U_NAND_B.5
NAND_OSPI_IO1: U_MPU.C16, U_NAND_A.2, U_NAND_B.2
NAND_OSPI_IO2: U_MPU.B16, U_NAND_A.3, U_NAND_B.3
NAND_OSPI_IO3: U_MPU.B15, U_NAND_A.7, U_NAND_B.7
NRST: C_MPU_NRST.1, P_companion_compute_spacer_power_board_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.36, R_MPU_NRST.2, U_MPU.N2
PMIC_PWR_OK: P_companion_compute_spacer_power_board_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.37, U_MPU.G1
PWR_HOLD: P_companion_compute_spacer_power_board_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.38, U_MPU.C11
QPD_TIA_A: J_FLEXL_companion_compute__qpd_module.3, U_MPU.B7
QPD_TIA_B: J_FLEXL_companion_compute__qpd_module.4, U_MPU.E4
QPD_TIA_C: J_FLEXL_companion_compute__qpd_module.5, U_MPU.F12
QPD_TIA_D: J_FLEXL_companion_compute__qpd_module.6, U_MPU.F7
RADAR_EN: J_companion_compute_spacer_companion_co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.13, U_MPU.D15
SWO: P_companion_compute_spacer_power_board_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.39, U_MPU.V1
SYS_I2C_SCL: P_companion_compute_spacer_power_board_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.40, U_MPU.J7
SYS_I2C_SDA: P_companion_compute_spacer_power_board_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.41, U_MPU.J9
SYS_SPI_CS_FIN: P_companion_compute_spacer_power_board_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.42, U_MPU.A12
SYS_SPI_MISO: P_companion_compute_spacer_power_board_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.43, U_MPU.C8
SYS_SPI_MOSI: P_companion_compute_spacer_power_board_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.44, U_MPU.E9
SYS_SPI_SCLK: P_companion_compute_spacer_power_board_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.45, U_MPU.B8
TMP1_ALERT: P_companion_compute_spacer_power_board_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.46, U_MPU.F9
USB_DM: J_companion_compute_spacer_companion_co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.14, U_MPU.V12
USB_DP: J_companion_compute_spacer_companion_co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.15, U_MPU.W12
USB_TXRTUNE: R_MPU_TXRTUNE.1, U_MPU.R15
USB_VBUS: J_companion_compute_spacer_companion_co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.16, J_companion_compute_spacer_companion_co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.19, P_companion_compute_spacer_power_board_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.47
USB_VBUS_DET: R_USB_VBUS_PD.2, U_MPU.W6
V08_CAP: C_MPU_V08CAP.1, U_MPU.M8
WBA_BOOT0: P_companion_compute_spacer_power_board_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.48, U_MPU.B11
WBA_HCI_IRQ: P_companion_compute_spacer_power_board_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.49, U_MPU.A8
WBA_HCI_MISO: P_companion_compute_spacer_power_board_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.50, U_MPU.E12
WBA_HCI_MOSI: P_companion_compute_spacer_power_board_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.51, U_MPU.A7
WBA_HCI_NSS: P_companion_compute_spacer_power_board_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.52, U_MPU.A16
WBA_HCI_SCK: P_companion_compute_spacer_power_board_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.53, U_MPU.A15
WBA_RST_CMD: P_companion_compute_spacer_power_board_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.54, U_MPU.A9
WBA_UART_RX: P_companion_compute_spacer_power_board_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.55, U_MPU.P12
WBA_UART_TX: P_companion_compute_spacer_power_board_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.56, U_MPU.M15
